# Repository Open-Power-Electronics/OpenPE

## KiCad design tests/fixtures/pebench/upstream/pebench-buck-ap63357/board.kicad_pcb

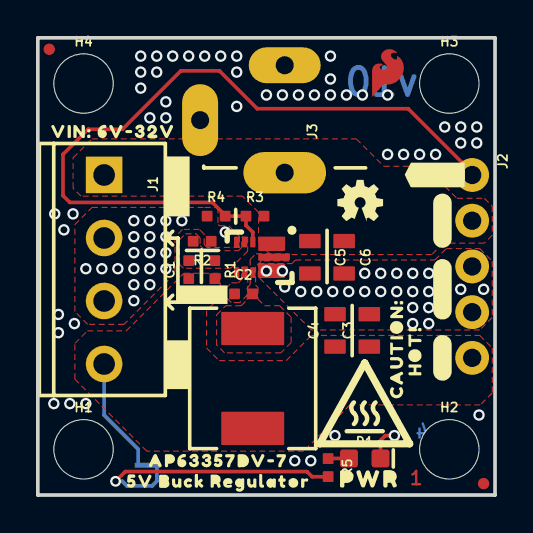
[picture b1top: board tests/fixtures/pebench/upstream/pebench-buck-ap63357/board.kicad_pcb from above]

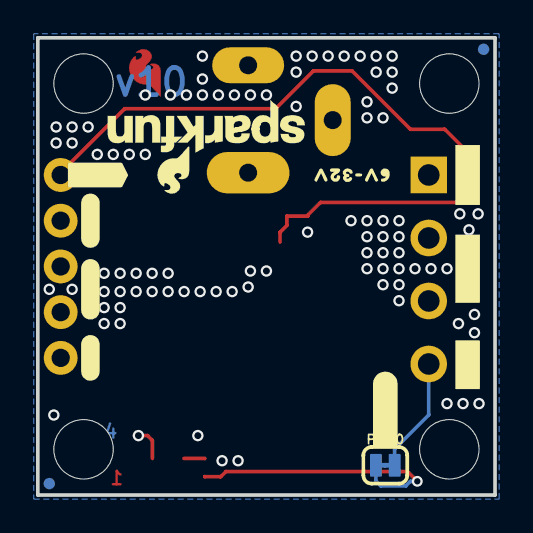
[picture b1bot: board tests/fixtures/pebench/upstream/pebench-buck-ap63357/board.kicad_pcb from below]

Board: 4 copper layers, 25.4 x 25.4 mm, 54 parts (13 on the bottom side), 9 nets.

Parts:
C1: 47pF; 0402-TIGHT
C2: 0.1uF; 0402-TIGHT
C3, C4: 22uF; 0805
C5, C6: 4.7uF; 0805
D1: RED; LED-0603
FD1, FD2, FD3, FD4: FIDUCIALUFIDUCIAL; FIDUCIAL-MICRO
FRAME1: FRAME-LEDGER; CREATIVE_COMMONS
H1, H2, H3, H4: STAND-OFF
J1: SCREWTERMINAL-3.5MM-4
J2: 1X05_NO_SILK
J3: POWER_JACK; POWER_JACK_PTH_SLOT_NO_OVRHNG_SILK
L1: 6.8UH; 07A7_6U8H
LOGO1: OSHW-LOGOMINI; OSHW-LOGO-MINI
LOGO2: SFE_LOGO_NAME_FLAME.1_INCH; SFE_LOGO_NAME_FLAME_.1
PWR0: JUMPER-SMT_2_NC_TRACE_SILK; SMT-JUMPER_2_NC_TRACE_SILK
R1: 220K; 0402-TIGHT
R2: 41.2K; 0402-TIGHT
R3: 93.1k; 0402-TIGHT
R4: 22k; 0402-TIGHT
R5: 2.2k; 0402-TIGHT
U1: AP63357; V-DFN3020-13
U$1: AP63357DV#70
U$2: 5V_BUCK_REGULATOR0
U$3: #5V#4
U$4: #VIN#8
U$5, U$13: #VIN#0
U$6, U$7: #GND#0
U$8, U$19: #EN_#0
U$9: #GND#9
U$10: #5V#10
U$11: 6V#32V10
U$12: HOT##0
U$14, U$24: #5V#0
U$15: #LED_#0
U$16: CAUTION#0
U$17: SFE_LOGO_FLAME_COPPER_EXPOSED_.1
U$18: VIN#_6V#32V0
U$20: PWR0
U$21: #GND#1
U$22: HIGH_TEMP_WARNING
U$23: ORDERING_INSTRUCTIONS
U$26: #VIN#3

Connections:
5V: C1.1, C3.1, C4.1, J1.4, J2.5, L1.P$2, PWR0.2, R1.2
EN: J2.1, R3.1, R4.2, U1.P$2
FB: C1.2, R1.1, R2.2, U1.P$3
GND: C3.2, C4.2, C5.2, C6.2, D1.C, J1.2, J1.3, J2.3, J2.4, J3.GND, R2.1, R4.1, U1.P$4, U1.P$8
unnamed: D1.A, R5.1
unnamed: C2.1, U1.P$6
unnamed: PWR0.1, R5.2
SW: C2.2, L1.P$1, U1.P$7, U1.P$9
VIN: C5.1, C6.1, J1.1, J2.2, J3.PWR, R3.2, U1.P$1

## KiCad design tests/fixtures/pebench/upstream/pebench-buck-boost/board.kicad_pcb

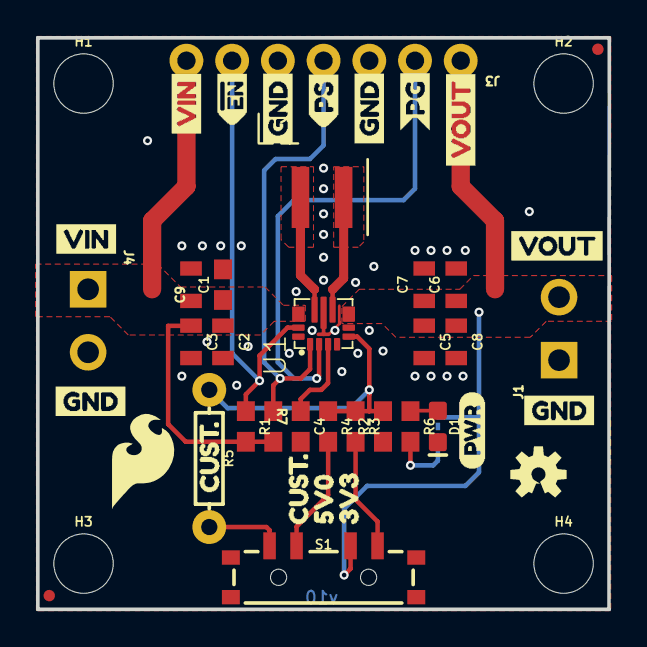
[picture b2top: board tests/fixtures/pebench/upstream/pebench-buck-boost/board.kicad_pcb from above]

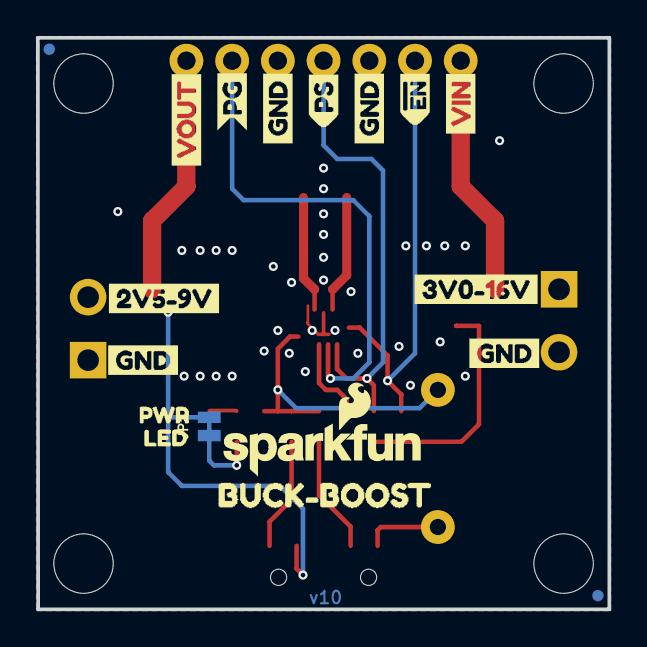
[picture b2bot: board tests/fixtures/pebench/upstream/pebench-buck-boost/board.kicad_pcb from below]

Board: 2 copper layers, 31.8 x 31.8 mm, 67 parts (18 on the bottom side), 15 nets.

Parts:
C1, C4: 0.1uF; 0603
C2, C3, C5, C9: 10uF; 0805
C6, C7, C8: 22uF; 0805
D1: RED; LED-0603
FD1, FD2, FD3, FD4: FIDUCIALUFIDUCIAL; FIDUCIAL-MICRO
FRAME1: FRAME-LETTER; CREATIVE_COMMONS
H1, H2, H3, H4: STAND-OFF
J1, J4: SCREWTERMINAL-3.5MM-2-NS
J3: 1X07_NO_SILK
JP1: SMT-JUMPER_2_NC_TRACE_NO-SILK
L1: 1.5uH; XFL4020
LOGO1: SFE_LOGO_NAME_FLAME.1_INCH; SFE_LOGO_NAME_FLAME_.1
LOGO2: OSHW-LOGOS; OSHW-LOGO-S
LOGO3: SPECIAL_INSTRUCTIONS-ORDERING; ORDERING_INSTRUCTIONS
R1, R7: 10k; 0603
R2: 68.1k; 0603
R3: 213k; 0603
R4: 365k; 0603
R5: CUSTOM; AXIAL-0.3
R6: 1k; 0603
S1: SWITCH_SP3T_SMD
U1: TPS63070; VQFN-15-HR(3X2.5)
U$1: PWR2
U$2, U$17: CUST#7
U$3, U$25: VIN0
U$4, U$20, U$30, U$31: GND1
U$5: VIN3
U$6, U$7, U$12, U$13: GND4
U$8: VOUT5
U$9: SFE_LOGO_FLAME_.2
U$10: 3V0#16V6
U$11: PWR1
U$14: 2V5#9V1
U$15: BUCK#BOOST18
U$16: LED0
U$18: 5V08
U$19: 3V39
U$21, U$26: VOUT2
U$22, U$28: #EN0
U$23, U$29: PS1
U$24, U$27: PG2

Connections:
FB: R2.2, R3.1, R4.1, R5.P$1, U1.P$5
GND: C1.2, C2.2, C3.2, C4.2, C5.2, C6.2, C7.2, C8.2, C9.2, D1.C, J1.1, J3.3, J3.5, J4.2, R2.1, U1.P$4, U1.P$6, U1.P$10, U1.P$15
unnamed: L1.P$1, U1.P$11
unnamed: L1.P$2, U1.P$9
unnamed: R5.P$2, S1.1
unnamed: R4.2, S1.2
unnamed: C4.1, U1.P$3
unnamed: R3.2, S1.4
unnamed: JP1.1, R6.2
unnamed: D1.A, R6.1
PG: J3.2, U1.P$2
PS: J3.4, R7.1, U1.P$1
VIN: C1.1, C2.1, C3.1, C9.1, J3.7, J4.1, R1.2, R7.2, U1.P$12/13
VOUT: C5.1, C6.1, C7.1, C8.1, J1.2, J3.1, JP1.2, S1.3, U1.P$7/8
~EN: J3.6, R1.1, U1.P$14

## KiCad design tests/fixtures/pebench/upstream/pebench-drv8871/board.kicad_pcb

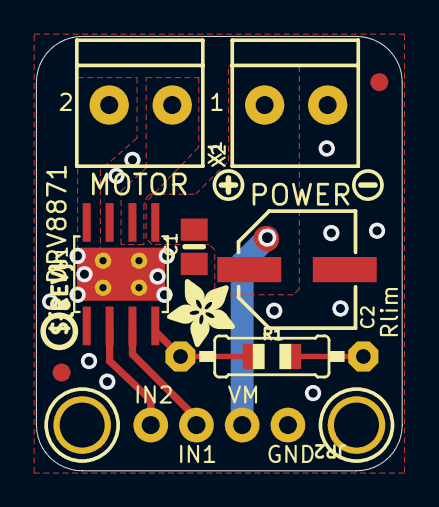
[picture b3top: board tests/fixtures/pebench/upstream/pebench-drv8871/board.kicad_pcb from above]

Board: 2 copper layers, 20.3 x 24.1 mm, 15 parts (0 on the bottom side), 7 nets.

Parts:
C1: 0.1uF/50V; 0805-NO
C2: 22uF/63V; PANASONIC_D
FID1, FID2: FIDUCIAL""; FIDUCIAL_1MM
JP2: 1X04_ROUND_76
R1: 30K; 0805-THM
U1: DRV8871; HSOP8
U$9, U$10: MOUNTINGHOLE2.5; MOUNTINGHOLE_2.5_PLATED
U$11: SYMBOL_PLUS
U$12: SYMBOL_MINUS
U$14: ADAFRUIT_3.5MM
U$15: PCBFEAT-REV-040
X1: DCMOTOR; TERMBLOCK_1X2-3.5MM
X2: POWER; TERMBLOCK_1X2-3.5MM

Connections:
GND: C1.2, C2.-, JP2.1, R1.1, U1.1, U1.7, U1.GND, U1.P$1, U1.P$2, U1.P$3, U1.P$4, X2.2
IN1: JP2.3, U1.3
IN2: JP2.4, U1.2
unnamed: R1.2, U1.4
OUT1: U1.6, X1.2
OUT2: U1.8, X1.1
VMOTOR: C1.1, C2.+, JP2.2, U1.5, X2.1

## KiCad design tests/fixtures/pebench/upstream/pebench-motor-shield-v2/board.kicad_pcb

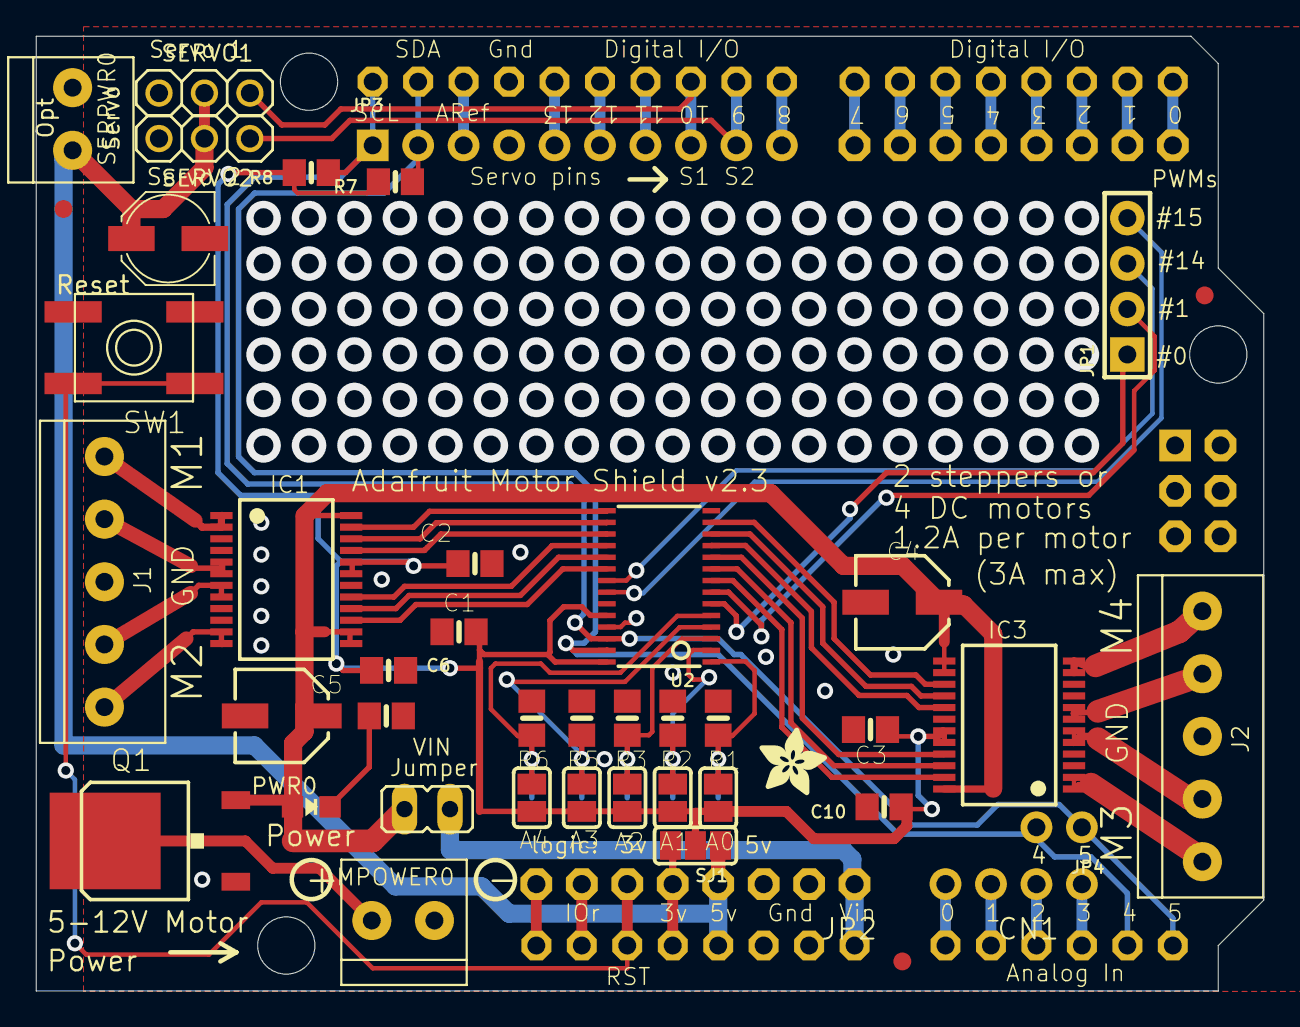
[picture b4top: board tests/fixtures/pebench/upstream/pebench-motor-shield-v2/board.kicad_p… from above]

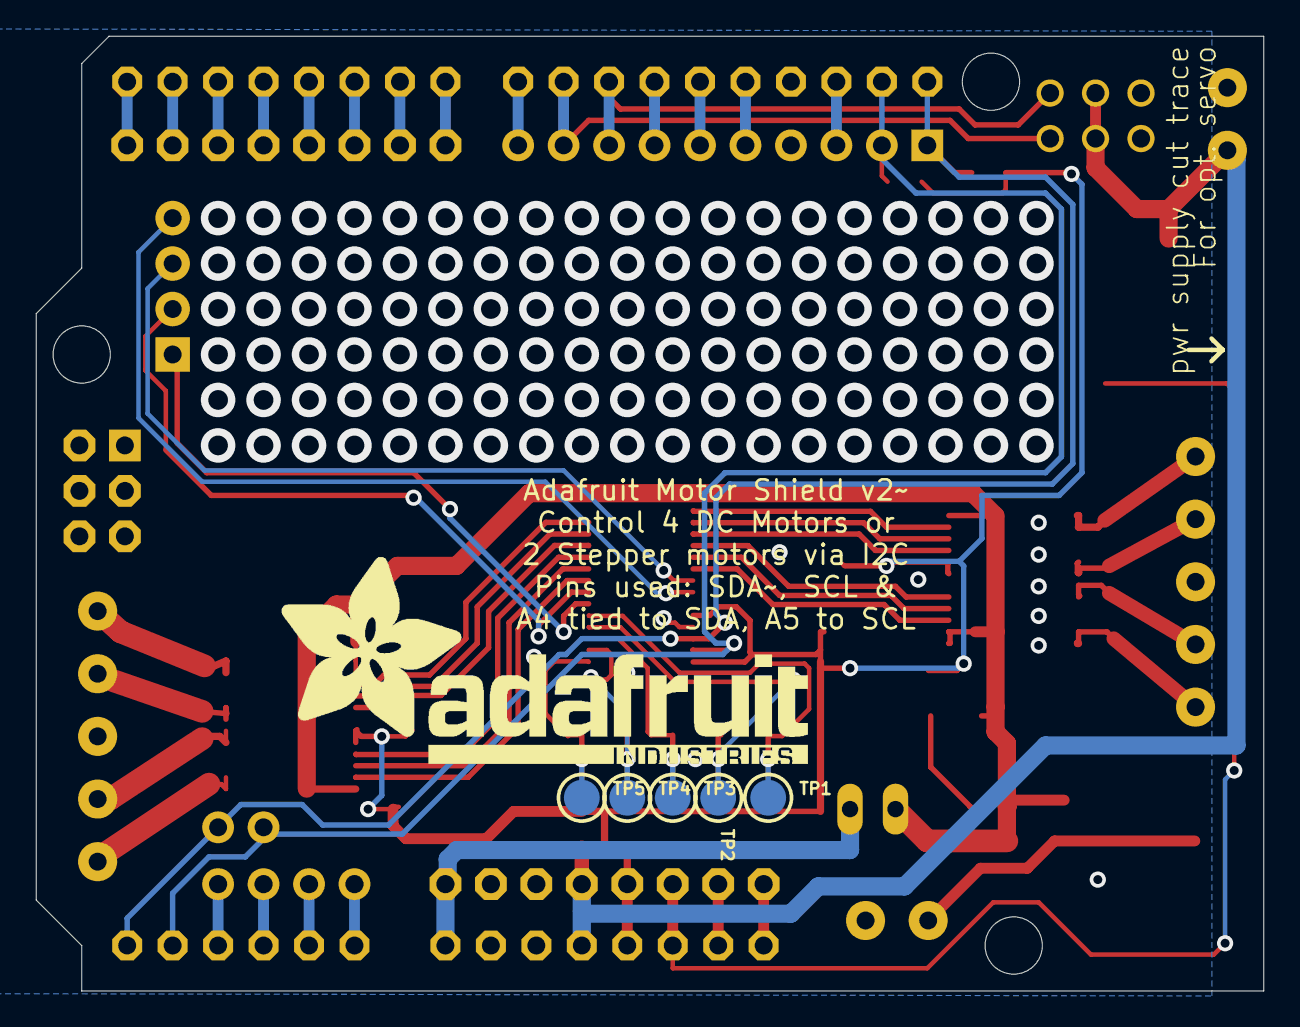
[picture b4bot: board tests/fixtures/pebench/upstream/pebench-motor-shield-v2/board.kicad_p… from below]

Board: 2 copper layers, 68.6 x 53.3 mm, 55 parts (6 on the bottom side), 61 nets.

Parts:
A0, A1, A2, A3, A4: SOLDERJUMPER_REFLOW_NOPASTE
C1, C2, C3: 0.1uF; 0805-NO
C4: 47uF/16v; PANASONIC_C
C5: 47uF+/16v; PANASONIC_C
C6, C10: 10uF; 0805-NO
C9: 10\0uF 6.3V; PANASONIC_C
CN1: 1X4-CLEANBIG; 1X04-CLEANBIG
D0-7: 1X08-CLEANBIG
IC1, IC3: TB6612FNG; SSOP24
J1, J2: 1X5; 1X05-3.5MM
JP1: 1X04_ROUND_76
JP2: 1X08-CLEANBIG
JP3: 1X10_ROUND70
JP4: 1X02_ROUND
LED1: Green; CHIPLED_0805_NOOUTLINE
MPOWER0: 1X2-3.5MM
PWR0: JP1
Q1: AOD417; D-PAK_TO252AA
R1, R2, R3, R5, R6: 10k; 0805-NO
R4: 1K; 0805-NO
R7, R8: 10K; 0805-NO
SERPWR0: 1X2-3.5MM
SERVO1, SERVO2: 1X03
SJ1: SOLDERJUMPER_2WAY_OPEN_NOPASTE
SW1: SPST_TACT-EVQQ2; EVQ-Q2
TP1, TP2, TP3, TP4, TP5: TESTPOINT_ROUND_2MM
U2: PCA9685; TSSOP28
U$1: ARDUINO_R3_ICSP; ARDUINOR3_ICSP
U$2, U$3, U$4: FIDUCIAL; FIDUCIAL_1MM
U$5: ADAFRUIT_TEXT_30MM
U$6: ADAFRUIT_3.5MM
UNK_HOLE_0: dummyfp0
UNK_HOLE_1: dummyfp1
UNK_HOLE_2: dummyfp2

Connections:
+3V3: JP2.5, SJ1.3, U$1.3V
+5V: C9.+, JP2.4, SERPWR0.1, SERVO1.2, SERVO2.2, SJ1.1, U$1.5V, U$1.5V_ICSP
+12V: C4.+, C5.+, IC1.13, IC1.14, IC1.24, IC3.13, IC3.14, IC3.24, LED1.A, PWR0.1, Q1.3
/RST: JP2.6, SW1.B, SW1.B', U$1.RESET, U$1.RESET_ICSP
A0: A0.2, R1.2, TP5.P$1, U2.1
A1: A1.2, R2.2, TP4.P$1, U2.2
A2: A2.2, R3.2, TP3.P$1, U2.3
A3: A3.1, R5.2, TP2.P$1, U2.4
A4: A4.1, R6.2, TP1.P$1, U2.5
AD0: CN1.4, U$1.A0
AD1: CN1.3, U$1.A1
AD2: CN1.2, U$1.A2
AD3: CN1.1, U$1.A3
AD4/SDA: JP3.2, JP4.2, R7.1, U2.27, U$1.A4, U$1.SDA
AD5/SCL: JP3.1, JP4.1, R8.1, U2.26, U$1.A5, U$1.SCL
AREF: JP3.3, U$1.AREF
D0: D0-7.1, U$1.D0
D1: D0-7.2, U$1.D1
D2: D0-7.3, U$1.D2
D3: D0-7.4, U$1.D3
D4: D0-7.5, U$1.D4
D5: D0-7.6, U$1.D5
D6: D0-7.7, U$1.D6
D7: D0-7.8, U$1.D7
D8: JP3.10, U$1.D8
D9: JP3.9, SERVO2.3, U$1.D9
D10: JP3.8, SERVO1.3, U$1.D10
D11: JP3.7, U$1.D11
D12: JP3.6, U$1.D12
D13: JP3.5, U$1.D13
GND: C1.2, C2.2, C3.2, C4.-, C5.-, C6.2, C9.-, C10.2, IC1.3, IC1.4, IC1.9, IC1.10, IC1.18, IC3.3, IC3.4, IC3.9, IC3.10, IC3.18, J1.3, J2.3, JP2.2, JP2.3, JP3.4, MPOWER0.1, Q1.1, R1.1, R2.1, R3.1, R4.1, R5.1, R6.1, SERPWR0.2, SERVO1.1, SERVO2.1, SW1.A, SW1.A', U2.14, U2.23, U2.25, U$1.GND, U$1.GND@1, U$1.GND@2, U$1.GND@3
IOREF: JP2.7, U$1.IOREF
M1A: IC1.1, IC1.2, J1.5
M1B: IC1.5, IC1.6, J1.4
M2A: IC1.11, IC1.12, J1.1
M2B: IC1.7, IC1.8, J1.2
M3A: IC3.1, IC3.2, J2.1
M3B: IC3.5, IC3.6, J2.2
M4A: IC3.11, IC3.12, J2.5
M4B: IC3.7, IC3.8, J2.4
unnamed: JP2.8, U$1.RESERVED
unnamed: LED1.C, R4.2
PWM0: JP1.1, U2.6
PWM1: JP1.2, U2.7
PWM2: IC3.23, U2.8
PWM3: IC3.22, U2.9
PWM4: IC3.21, U2.10
PWM5: IC3.17, U2.11
PWM6: IC3.16, U2.12
PWM7: IC3.15, U2.13
PWM8: IC1.23, U2.15
PWM9: IC1.22, U2.16
PWM10: IC1.21, U2.17
PWM11: IC1.17, U2.18
PWM12: IC1.16, U2.19
PWM13: IC1.15, U2.20
PWM14: JP1.3, U2.21
PWM15: JP1.4, U2.22
VCC: A0.1, A1.1, A2.1, A3.2, A4.2, C1.1, C2.1, C3.1, C6.1, C10.1, IC1.19, IC1.20, IC3.19, IC3.20, R7.2, R8.2, SJ1.2, U2.24, U2.28
VIN: JP2.1, PWR0.2, U$1.VIN
VMOTOR: MPOWER0.2, Q1.4

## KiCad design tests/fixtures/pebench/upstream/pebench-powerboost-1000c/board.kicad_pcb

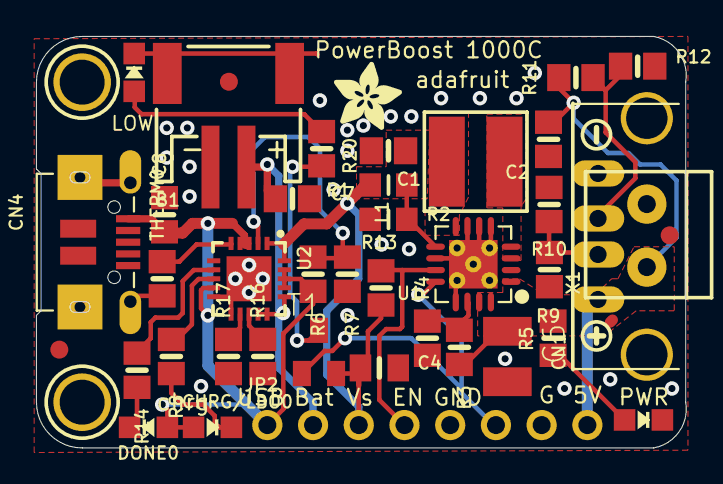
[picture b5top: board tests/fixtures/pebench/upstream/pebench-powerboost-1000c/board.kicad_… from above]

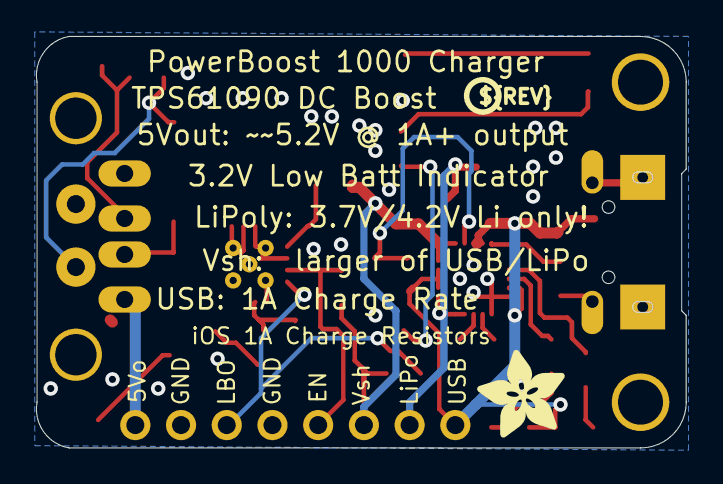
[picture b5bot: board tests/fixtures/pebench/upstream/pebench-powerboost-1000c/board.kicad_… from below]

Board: 2 copper layers, 36.1 x 22.9 mm, 47 parts (2 on the bottom side), 23 nets.

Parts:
B1: JST 2-PH; JSTPH2
C1, C7, C8: 10uF; 0805-NO
C2: 2.2uF; 0805-NO
C4: 0.1uF; 0805_10MGAP
C6: 100uF; C1210
CHRG/LBO0: ORANGE; CHIPLED_0805_NOOUTLINE
CN1: USBA_FEMALE; USB_HOST-PTH
CN4: MicroUSB; 4UCONN_20329
DONE0: GREEN; CHIPLED_0805_NOOUTLINE
FID1, FID2, FID3: FIDUCIAL""; FIDUCIAL_1MM
JP2: 1X08_ROUND
L1: 6.8uH; INDUCTOR_5X5MM_TDK_VLC5045
LED1: RED; CHIPLED_0805_NOOUTLINE
LED2: BLUE; CHIPLED_0805_NOOUTLINE
R1: 1.87M; _0805MP
R2: 340K; _0805MP
R3: 1.87M; 0805-NO
R4, R13: 200K; 0805-NO
R5, R8, R14, R20: 1K; 0805-NO
R6: 270K; 0805-NO
R7, R17: 100K; 0805-NO
R9: 43K; 0805-NO
R10: 49.9K; 0805-NO
R11: 75K 1%; 0805-NO
R12: 49.9K 1%; 0805-NO
R16: 1.0K; 0805-NO
T1: MMUN2133LT1G; SC59-BEC
THERM0: 15K; 0805-NO
U1: TPS61090RSAR; PVQFN-16
U2: MCP73871; QFN20_4MM
U$10, U$11: MOUNTINGHOLE2.5; MOUNTINGHOLE_2.5_PLATED
U$12: PCBFEAT-REV-040
U$25: SYMBOL_PLUS
U$26: SYMBOL_MINUS
U$28: ADAFRUIT_5MM
U$45: ADAFRUIT_3.5MM
X1: TERMBLOCK_1X2-3.5MM

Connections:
5.0V: C2.1, C6.1, CN1.VBUS, JP2.8, R3.2, R5.1, R9.2, R11.2, U1.1, U1.15, U1.16, X1.2
D+: CN1.D+, R11.1, R12.1
D-: CN1.D-, R9.1, R10.1
ENABLE: JP2.4, R13.2, U1.11
GND: B1.1, C1.2, C2.2, C4.2, C6.2, C7.2, C8.2, CN1.GND, CN4.BASE@1, CN4.BASE@2, CN4.GND, CN4.SPRT@1, CN4.SPRT@2, CN4.SPRT@3, CN4.SPRT@4, JP2.5, JP2.7, LED1.C, LED2.C, R2.1, R4.1, R7.2, R10.2, R12.2, R16.1, R17.1, THERM0.1, U1.5, U1.6, U1.7, U1.10, U1.13, U1.P$18, U1.P$19, U1.P$20, U1.P$21, U1.P$22, U1.THERMAL, U2.P$10, U2.P$11, U2.P$21, X1.1
LBO: JP2.6, T1.B, U1.12
unnamed: L1.P$2, U1.3, U1.4
unnamed: LED1.A, R20.1
unnamed: R1.1, R2.2, U1.9
unnamed: LED2.A, R5.2
unnamed: R3.1, R4.2, U1.14
unnamed: R20.2, T1.C
unnamed: R6.1, R7.1, U2.P$2
unnamed: DONE0.C, R14.2
unnamed: R14.1, U2.P$7
unnamed: THERM0.2, U2.P$5
unnamed: R8.1, U2.P$8
unnamed: CHRG/LBO0.C, R8.2
unnamed: R17.2, U2.P$12
unnamed: R16.2, U2.P$13
VBAT: C1.1, C4.1, JP2.3, L1.P$1, R1.2, R13.1, T1.E, U1.8, U2.P$1, U2.P$20
VBUS: C8.1, CHRG/LBO0.A, CN4.VBUS, DONE0.A, JP2.1, R6.2, U2.P$3, U2.P$4, U2.P$9, U2.P$17, U2.P$18, U2.P$19
VLIPO: B1.2, C7.1, JP2.2, U2.P$14, U2.P$15, U2.P$16

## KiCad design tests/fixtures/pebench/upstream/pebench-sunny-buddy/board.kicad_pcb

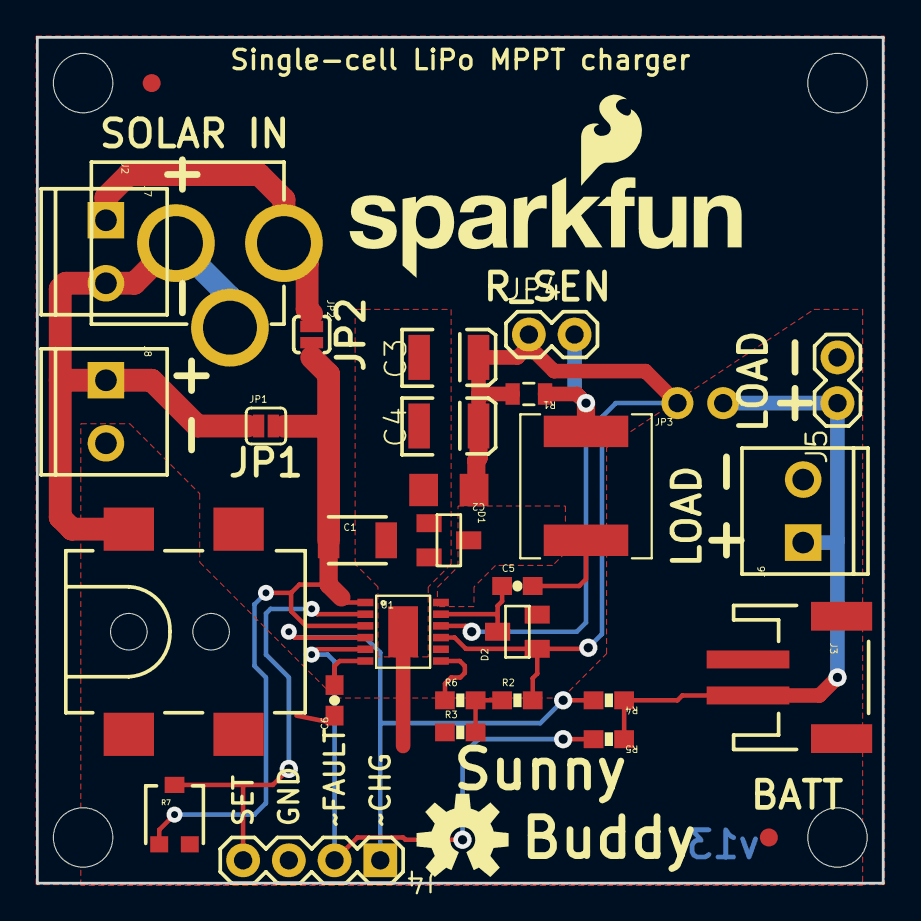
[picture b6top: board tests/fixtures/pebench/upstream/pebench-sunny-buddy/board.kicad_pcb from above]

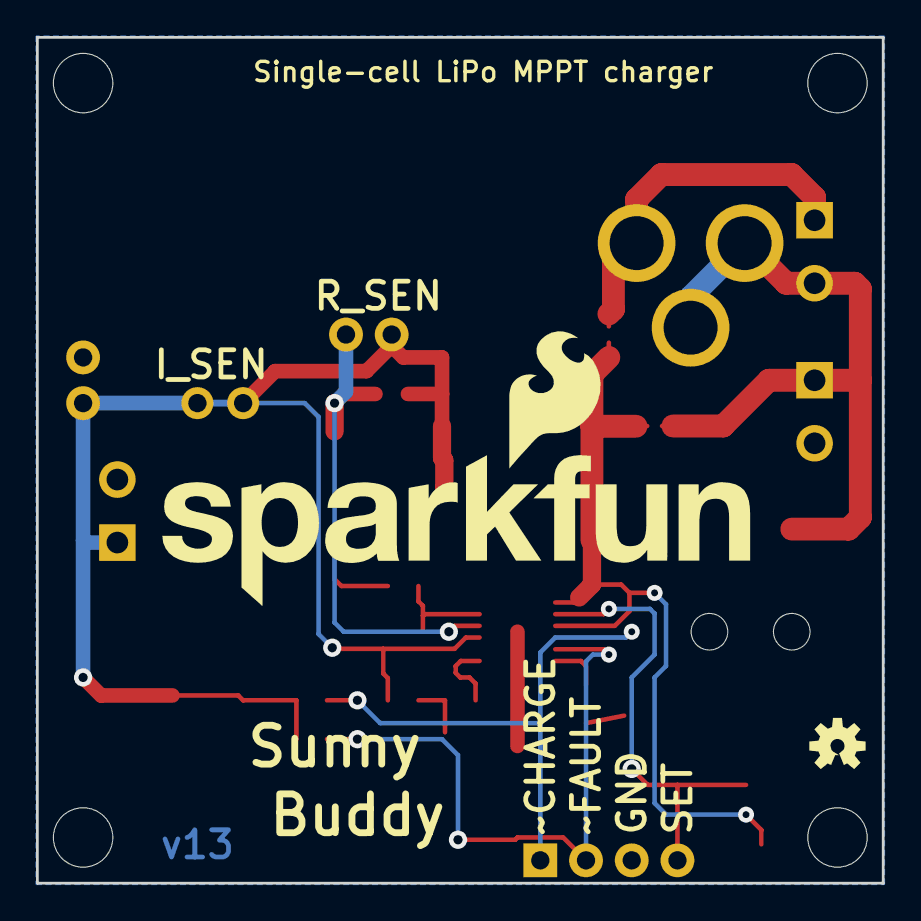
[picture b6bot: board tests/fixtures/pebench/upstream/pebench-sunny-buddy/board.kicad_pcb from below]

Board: 2 copper layers, 47.0 x 47.0 mm, 40 parts (2 on the bottom side), 15 nets.

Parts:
C1: 10uF; 1210
C2: 10uF; 1206
C3, C4: 47uF; EIA3528
C5, C6: 1.0uF; 0603-CAP
D1, D2: ZLLS500; SOT23
FID1, FID2: FIDUCIAL1X2; FIDUCIAL-1X2
FRAME1: FRAME-LETTER; CREATIVE_COMMONS
J1: 5.5x2.1mm Barrel; POWER_JACK_SMD
J2: POWER_JACKPTH; POWER_JACK_PTH
J3: JST-2-SMD
J4: 1X04
J5: M02PTH; 1X02
J6, J7, J8: M023.5MM; SCREWTERMINAL-3.5MM-2
JP1: SJ_2S
JP2: SJ_2S-NO
JP3: JUMPER-PTH-2-NC; PTH-JUMPER-NC_BOTTOM_NO_SILK
JP4: R_SEN; 1X02
L1: 68uH; CR75
LOGO1: SFE_LOGO_NAME_FLAME.2_INCH; SFE_LOGO_NAME_FLAME_.2
LOGO2: OSHW-LOGOM; OSHW-LOGO-M
LOGO3: OSHW-LOGOS; OSHW-LOGO-S
LOGO4: SFE_LOGO_NAME_FLAME.3_INCH; SFE_LOGO_NAME_FLAME_.3
R1: 0.22; 0805
R2: 47k; 0603-RES
R3, R6: 220k; 0603-RES
R4, R5: 10K; 0603-RES
R7: 10k; TRIMPOT-3MM
STANDOFF1, STANDOFF2, STANDOFF3, STANDOFF4: STAND-OFF
U1: LT3652; MSOP-12_GND

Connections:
BOOST: C5.1, D2.3, U1.11
FB: R2.1, R3.2, R6.2
GND: C1.2, C2.2, C3.C, C4.C, C6.1, D1.1, J1.GND, J1.P$4, J3.1, J3.NC1, J3.NC2, J4.3, J5.2, J6.2, J8.2, R3.1, R7.3, U1.13
unnamed: R6.1, U1.7
unnamed: C2.1, C3.A, C4.A, D2.1, JP3.1, JP4.1, R1.2, R2.2, U1.9
unnamed: J1.VIN0, J2.GND, J2.GNDBREAK, J7.2, J8.1, JP1.1
SENSE: JP4.2, L1.P$2, R1.1, U1.10
SET: J4.4, R7.2, U1.2
SFSASDF: J2.PWR, J7.1, JP2.1
SW: C5.2, D1.3, L1.P$1, U1.12
TIMER: C6.2, U1.6
VIN: C1.1, JP1.2, JP2.2, R7.1, U1.1, U1.3
V_BATT: J3.2, J5.1, J6.1, JP3.2, R4.1, R5.1
~CHRG: J4.1, R4.2, U1.4
~FAULT: J4.2, R5.2, U1.5

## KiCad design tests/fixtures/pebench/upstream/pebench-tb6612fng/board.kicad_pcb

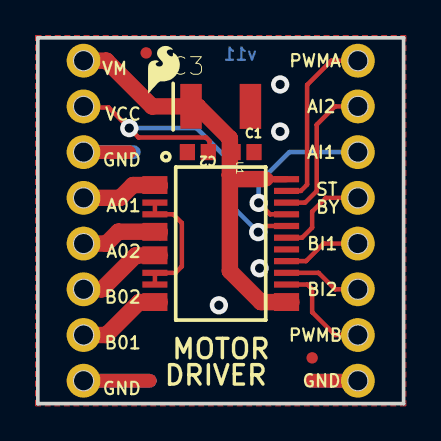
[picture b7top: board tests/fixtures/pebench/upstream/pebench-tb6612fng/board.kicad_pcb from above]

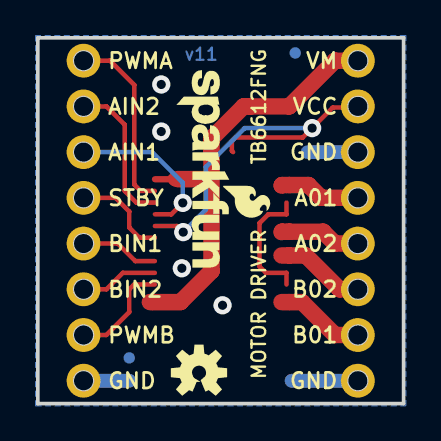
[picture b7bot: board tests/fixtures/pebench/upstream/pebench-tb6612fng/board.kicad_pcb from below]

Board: 2 copper layers, 20.3 x 20.3 mm, 14 parts (4 on the bottom side), 14 nets.

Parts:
C1, C2: 0.1uF; 0402
C3: 10uF; EIA3528
FD1, FD2, FD3, FD4: FIDUCIALUFIDUCIAL; FIDUCIAL-MICRO
FRAME1: FRAME-LETTER; CREATIVE_COMMONS
JP1, JP2: 1X08_OFFSET_REDUCED
LOGO1: SFE_LOGO_FLAME.1_INCH; SFE_LOGO_FLAME_.1
LOGO2: OSHW-LOGOS; OSHW-LOGO-S
LOGO4: SFE_LOGO_NAME_FLAME.1_INCH; SFE_LOGO_NAME_FLAME_.1
U1: TB6612FNG; SSOP24

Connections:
A01: JP1.5, U1.1, U1.2
A02: JP1.4, U1.5, U1.6
AIN1: JP2.3, U1.21
AIN2: JP2.2, U1.22
B01: JP1.2, U1.11, U1.12
B02: JP1.3, U1.7, U1.8
BIN1: JP2.5, U1.17
BIN2: JP2.6, U1.16
GND: C1.2, C2.2, C3.C, JP1.1, JP1.6, JP2.8, U1.3, U1.4, U1.9, U1.10, U1.18
PWMA: JP2.1, U1.23
PWMB: JP2.7, U1.15
STBY: JP2.4, U1.19
VCC: C2.1, JP1.7, U1.20
VM: C1.1, C3.A, JP1.8, U1.13, U1.14, U1.24

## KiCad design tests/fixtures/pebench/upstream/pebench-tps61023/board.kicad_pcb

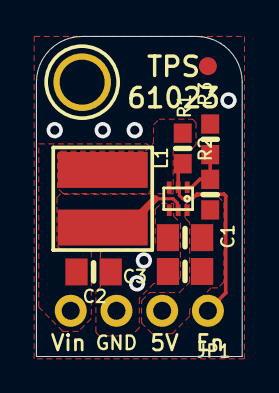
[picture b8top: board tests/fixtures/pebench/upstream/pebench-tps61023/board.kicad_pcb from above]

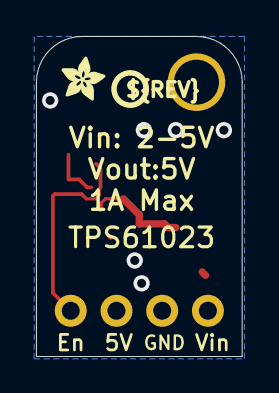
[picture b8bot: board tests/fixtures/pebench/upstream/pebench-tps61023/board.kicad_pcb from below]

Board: 2 copper layers, 11.4 x 17.8 mm, 13 parts (2 on the bottom side), 6 nets.

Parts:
C1, C2, C3: 22uF; 0805-NO
FID1: FIDUCIAL_1MM
IC1: TPS61023; SOT563
JP1: 1X04_ROUND
L1: 1uH; INDUCTOR_5X5MM_TDK_VLC5045
R1, R3: 100K; 0603-NO
R2: 732K; 0603-NO
U$9: MOUNTINGHOLE2.5; MOUNTINGHOLE_2.5_PLATED
U$10: PCBFEAT-REV-040
U$11: ADAFRUIT_2.5MM

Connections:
EN: IC1.2, JP1.1, R1.2
FB: IC1.1, R2.2, R3.1
GND: C1.2, C2.2, C3.2, IC1.4, JP1.3, R3.2
SW: IC1.5, L1.P$2
VDD: C1.1, C3.1, IC1.6, JP1.2, R2.1
VIN: C2.1, IC1.3, JP1.4, L1.P$1, R1.1

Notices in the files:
parts and their libraries:
Released under the Creative Commons Attribution Share-Alike 4.0 License
https://creativecommons.org/licenses/by-sa/4.0
Released under the Creative Commons Attribution Share-Alike 3.0 License
http://creativecommons.org/licenses/by-sa/3.0
